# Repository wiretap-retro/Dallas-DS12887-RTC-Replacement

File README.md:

# Dallas DS12887 RTC Replacement
A simple Dallas DS12887 replacement board with enable/disable function and ext_batt header.

\

## Info
This Dallas DS12887 replacement utilizes a DS12885T+ TQFP-32 chip and a CR1220 battery holder. There is an enable/disable pin for you to save battery while the computer is in storage, and there's also an EXT_BATT header for hooking up an external battery holder if you don't want to use a CR1220 battery.

## Compatibility
Compatible with DS12887, DS1285 and DS1287 RTC's. Check datasheet for additional info: https://www.mouser.com/datasheet/2/256/DS12885-DS12C887A-1512672.pdf
\
\
Dallas -85 model numbers are just the bare RTC chip. Dallas -87 model numbers are the chip in an encapsulated package with the battery and crystal. Example: The Dallas DS14285 with a crystal and battery is the same thing as a DS14287 (compatible with the DS1287, which is actually just a DS1285 with a crystal and battery).

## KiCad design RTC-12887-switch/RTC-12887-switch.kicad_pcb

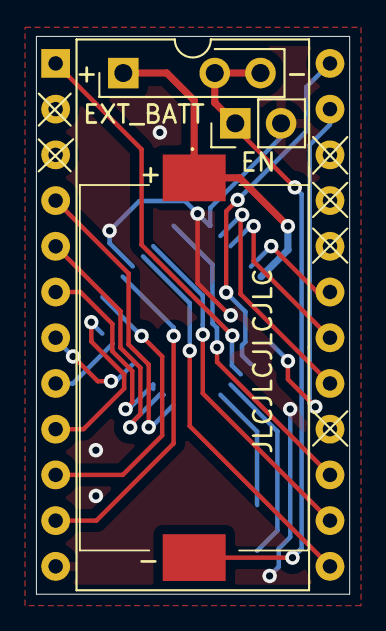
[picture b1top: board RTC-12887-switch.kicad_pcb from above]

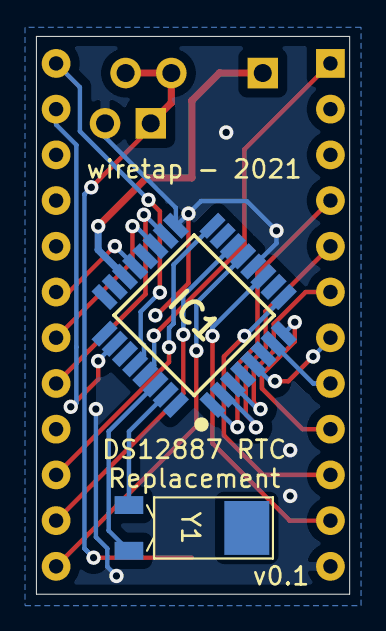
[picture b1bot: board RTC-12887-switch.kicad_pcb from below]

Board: 2 copper layers, 17.4 x 31.0 mm, 6 parts (2 on the bottom side), 22 nets.

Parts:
EN: PWR; PinHeader_1x02_P2.54mm_Vertical
IC1: DS12885T+; QFP80P900X900X120-32N
IC2: DS12887+; DIP-24_W15.24mm
J1: EXT_BATT
U1: SMTU1220-LF; SMTU1225LF
Y1: Crystal; Crystal_SMD_FrontierElectronics_FM206

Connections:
/AD0: IC1.1, IC2.4
/AD1: IC1.2, IC2.5
/AD2: IC1.3, IC2.6
/AD3: IC1.5, IC2.7
/AD4: IC1.7, IC2.8
/AD5: IC1.8, IC2.9
/AD6: IC1.9, IC2.10
/AD7: IC1.11, IC2.11
/AS: IC1.14, IC2.14
/BC: IC1.22, J1.1, U1.1
/COM: EN.1, J1.3, J1.4, U1.2
/CS: IC1.13, IC2.13
/DS: IC1.18, IC2.17
/IRQ: IC1.21, IC2.19
/MOT: IC1.29, IC2.1
/RESET: IC1.19, IC2.18
/RW: IC1.16, IC2.15
/SQW: IC1.26, IC2.23
/VCC: IC1.28, IC2.24
/X1: IC1.30, Y1.1
/X2: IC1.31, Y1.2
GND: EN.2, IC1.12, IC1.17, IC2.12

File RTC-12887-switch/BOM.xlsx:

Reference | Value | Footprint | Description | Manufacturer Name | Manufacturer Part Number | Mouser Part Number
Y1 | Crystal | 2-lead cylinder | 32.768 kHz Crystal | ECS | ECS-.327-6-13FLX-C-TR | 520-27-6-13FLX-C-TR
U1 | SMTU1220-LF | CR1220 Battery Holder | Coin Cell Battery Holders SFC MNT FOR CR1220 | RENATA | SMTU1220-LF | 614-SMTU1220-LF
IC1 | DS12885T+ | TQFP-32 | Real Time Clock RTC | Maxim Integrated | DS12885T+ | 700-DS12885T
Pin Headers (use a 1-row 2.54mm breakaway pin header)
Two 1x12 for the DS12887 holes that go into the motherboard (remove pins with "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
One 1x2 for the enable pin (this enable pin will cut off battery power for long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
One 1x4 for the EXT_BATT header (optional if you want to use that header with a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
Jumpers (2.54mm spacing)
One 1x2 jumper for the enable jumper. Optionally, you can solder the two pads t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
